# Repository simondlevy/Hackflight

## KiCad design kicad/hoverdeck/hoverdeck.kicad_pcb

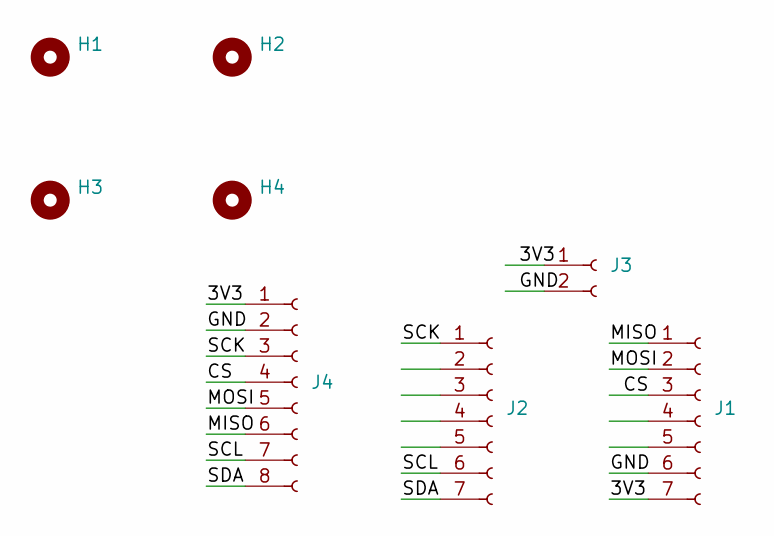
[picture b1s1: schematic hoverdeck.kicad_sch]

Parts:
H1, H2, H3, H4: MountingHole; MountingHole_2.5mm
J1, J2: Conn_01x07_Socket; PinSocket_1x07_P2.54mm_Vertical
J3: Conn_01x02_Socket; PinSocket_1x02_P2.54mm_Vertical
J4: Conn_01x08_Socket; PinSocket_1x08_P2.00mm_Vertical

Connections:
/3V3: J1.7, J3.1, J4.1
/CS: J1.3, J4.4
/GND: J1.6, J3.2, J4.2
/MISO: J1.1, J4.6
/MOSI: J1.2, J4.5
/SCK: J2.1, J4.3
/SCL: J2.6, J4.7
/SDA: J2.7, J4.8

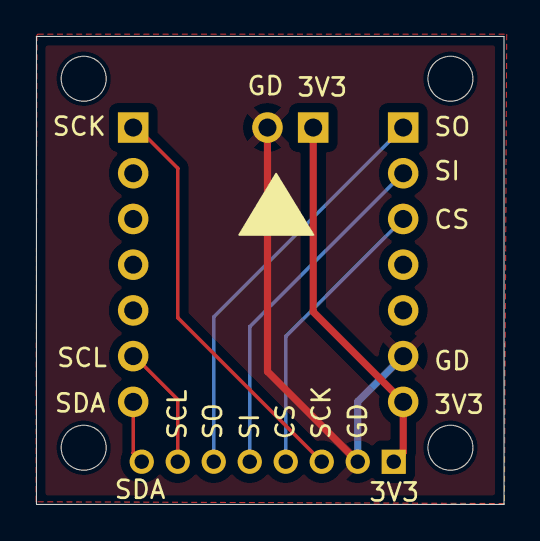
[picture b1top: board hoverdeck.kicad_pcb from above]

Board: 2 copper layers, 26.0 x 26.0 mm, 8 parts (0 on the bottom side), 8 nets.

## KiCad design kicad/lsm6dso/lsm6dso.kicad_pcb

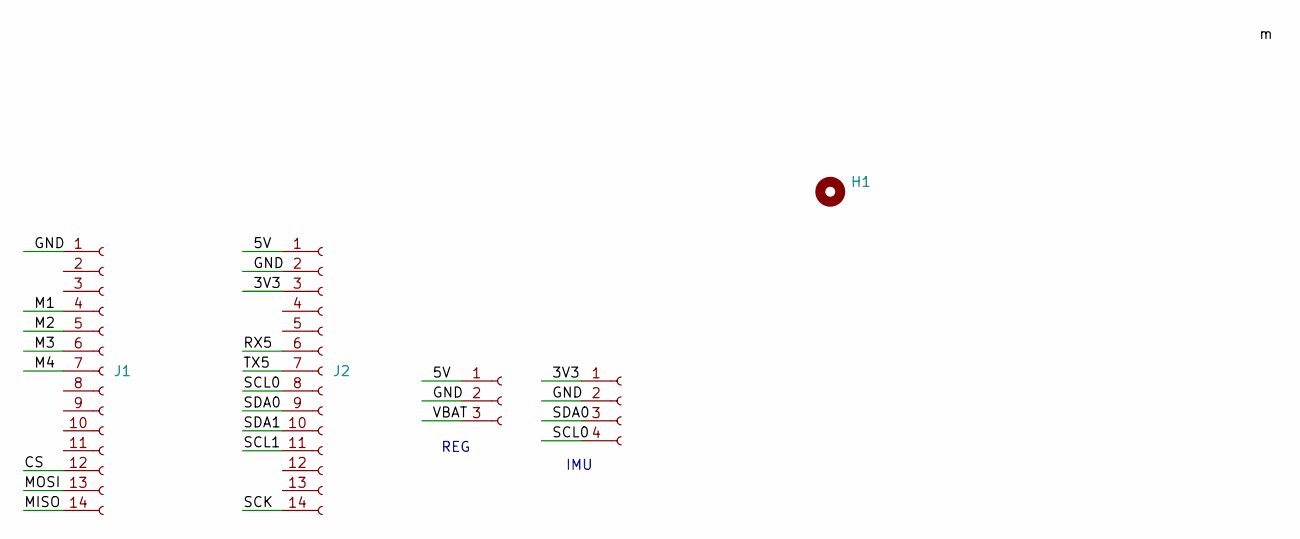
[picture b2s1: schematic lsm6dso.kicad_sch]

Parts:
H1: MountingHole; MountingHole_2.5mm
J1, J2: Conn_01x14_Socket; PinSocket_1x14_P2.54mm_Vertical
J4: Conn_01x03_Socket; PinHeader_1x03_P2.54mm_Vertical
J7: Conn_01x04_Socket; PinHeader_1x04_P2.54mm_Vertical

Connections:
/3V3: J2.3, J7.1
/5V: J2.1, J4.1
/CS: J1.12
/GND: J1.1, J2.2, J4.2, J7.2
/M1: J1.4
/M2: J1.5
/M3: J1.6
/M4: J1.7
/MISO: J1.14
/MOSI: J1.13
/RX5: J2.6
/SCK: J2.14
/SCL0: J2.8, J7.4
/SCL1: J2.11
/SDA0: J2.9, J7.3
/SDA1: J2.10
/TX5: J2.7
/VBAT: J4.3

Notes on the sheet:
REG
IMU

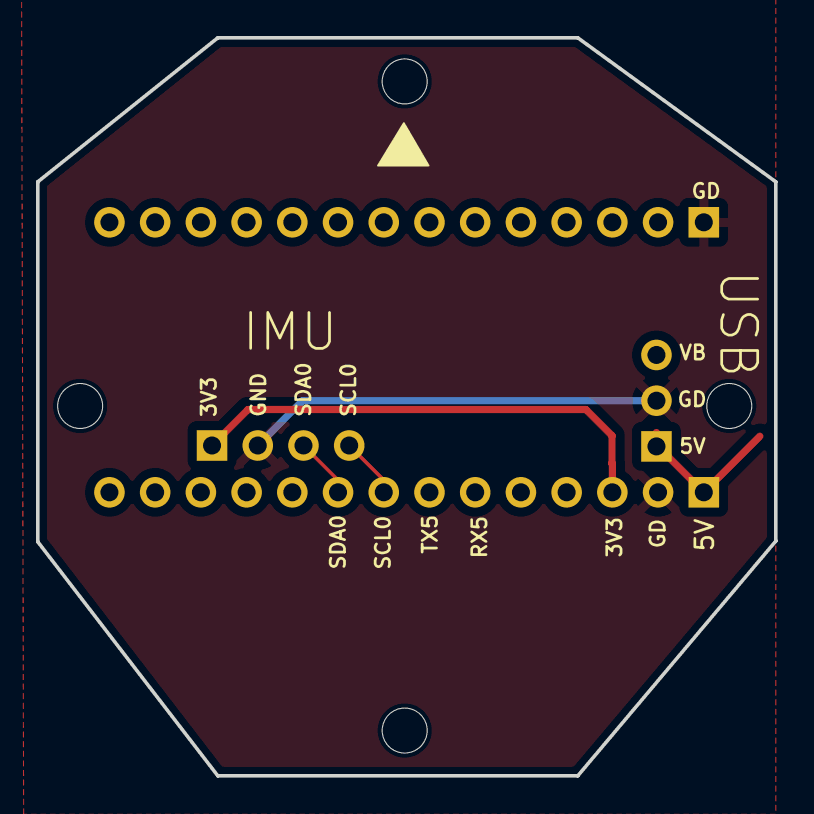
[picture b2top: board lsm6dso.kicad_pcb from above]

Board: 2 copper layers, 41.0 x 41.0 mm, 6 parts (0 on the bottom side), 5 nets.

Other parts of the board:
H1#2: MountingHole; MountingHole_2.5mm

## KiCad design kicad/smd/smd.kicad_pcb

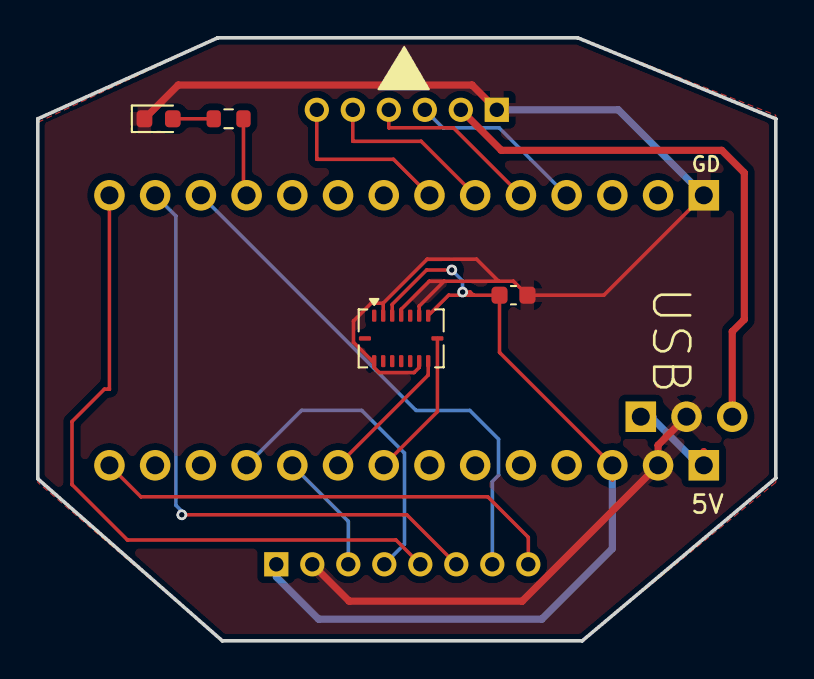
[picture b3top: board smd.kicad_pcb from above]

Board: 2 copper layers, 41.0 x 33.5 mm, 9 parts (0 on the bottom side), 18 nets.

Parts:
C1: C; C_0603_1608Metric
D1: LED; LED_0603_1608Metric
J1: Conn_01x14; PinSocket_1x14_P2.54mm_Vertical
J2: Conn_01x14_Socket; PinSocket_1x14_P2.54mm_Vertical
J4: Conn_01x03_Socket; PinHeader_1x03_P2.54mm_Vertical
J5: Conn_01x06; PinSocket_1x06_P2.00mm_Vertical
J6: Conn_01x08; PinSocket_1x08_P2.00mm_Vertical
R1: R; R_0603_1608Metric
U1: BMI088; Bosch_LGA-16_4.5x3mm_P0.5mm_LayoutBorder7x1y_ClockwisePinNu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

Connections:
/3V3: C1.2, J2.3, J6.1, U1.3 (VDD), U1.7 (PS)
/5V: J2.1, J4.1
/CS: J1.12, J6.7
/GND: C1.1, D1.1 (K), J1.1, J2.2, J4.2, J5.1, J6.2, U1.2 (GNDA), U1.4 (GNDA), U1.6 (GNDIO), U1.10 (SDO2), U1.15 (SDO1)
/LED: J1.11, R1.2
/M1: J1.4, J5.3
/M2: J1.5, J5.4
/M3: J1.6, J5.5
/M4: J1.7, J5.6
/MISO: J1.14, J6.5
/MOSI: J1.13, J6.6
/SCK: J2.14, J6.8
/SCL0: J2.8, U1.8 (SCK/SCL)
/SCL1: J2.11, J6.4
/SDA0: J2.9, U1.9 (SDI/SDA)
/SDA1: J2.10, J6.3
/VBAT: J4.3, J5.2
unnamed: D1.2 (A), R1.1

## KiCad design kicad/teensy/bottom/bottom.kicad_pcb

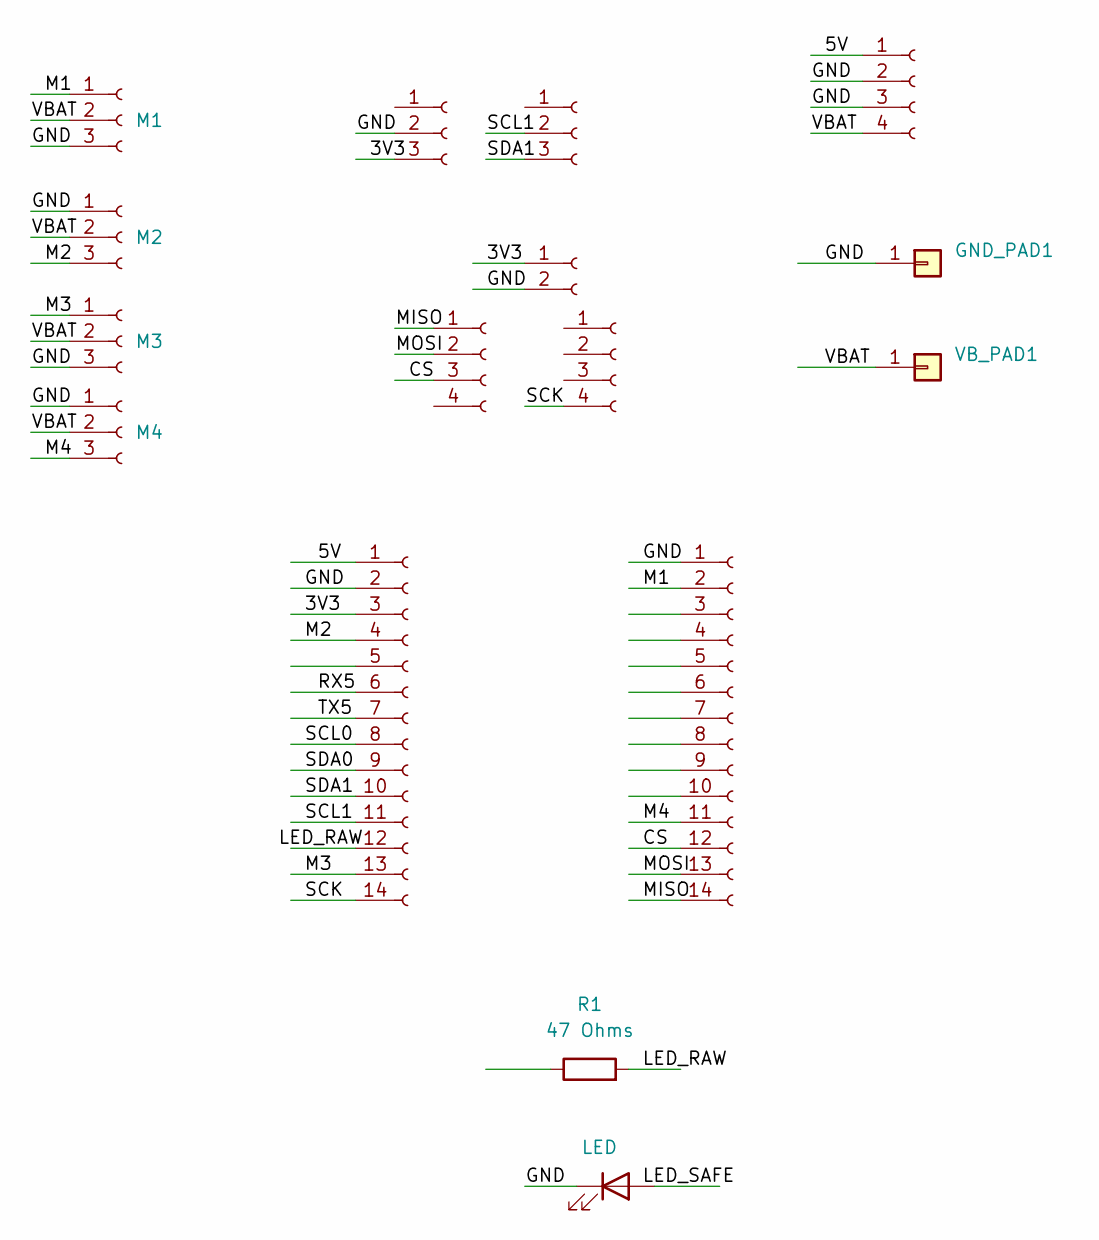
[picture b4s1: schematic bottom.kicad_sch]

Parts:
D1: LED; LED_D3.0mm
GND_PAD1: Conn_01x01; SolderWirePad_1x01_SMD_5x10mm
J1, J6, J8: Conn_01x04_Socket; PinSocket_1x04_P2.54mm_Vertical
J2, J7: Conn_01x03_Socket; PinSocket_1x03_P2.54mm_Vertical
J3: Conn_01x02_Socket; PinSocket_1x02_P2.54mm_Vertical
J4, J5: Conn_01x14_Socket; PinSocket_1x14_P2.54mm_Vertical
M1, M2, M3, M4: Conn_01x03_Socket; PinSocket_1x03_P2.54mm_Vertical
R1: 47 Ohms; R_Axial_DIN0204_L3.6mm_D1.6mm_P5.08mm_Horizontal
VB_PAD1: Conn_01x01; SolderWirePad_1x01_SMD_5x10mm

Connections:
/3V3: J2.3, J3.1, J4.3
/5V: J4.1, J8.1
/CS: J5.12, J6.3
/GND: D1.1 (K), GND_PAD1.1, J2.2, J3.2, J4.2, J5.1, J8.2, J8.3, M1.3, M2.1, M3.3, M4.1
/LED_RAW: R1.2
/M1: J5.2, M1.1
/M2: J4.4, M2.3
/M3: J4.13, M3.1
/M4: J5.11, M4.3
/MISO: J5.14, J6.1
/MOSI: J5.13, J6.2
/RX5: J4.6
/SCK: J1.4, J4.14
/SCL0: J4.8
/SCL1: J4.11, J7.2
/SDA0: J4.9
/SDA1: J4.10, J7.3
/TX5: J4.7
/VBAT: J8.4, M1.2, M2.2, M3.2, M4.2, VB_PAD1.1

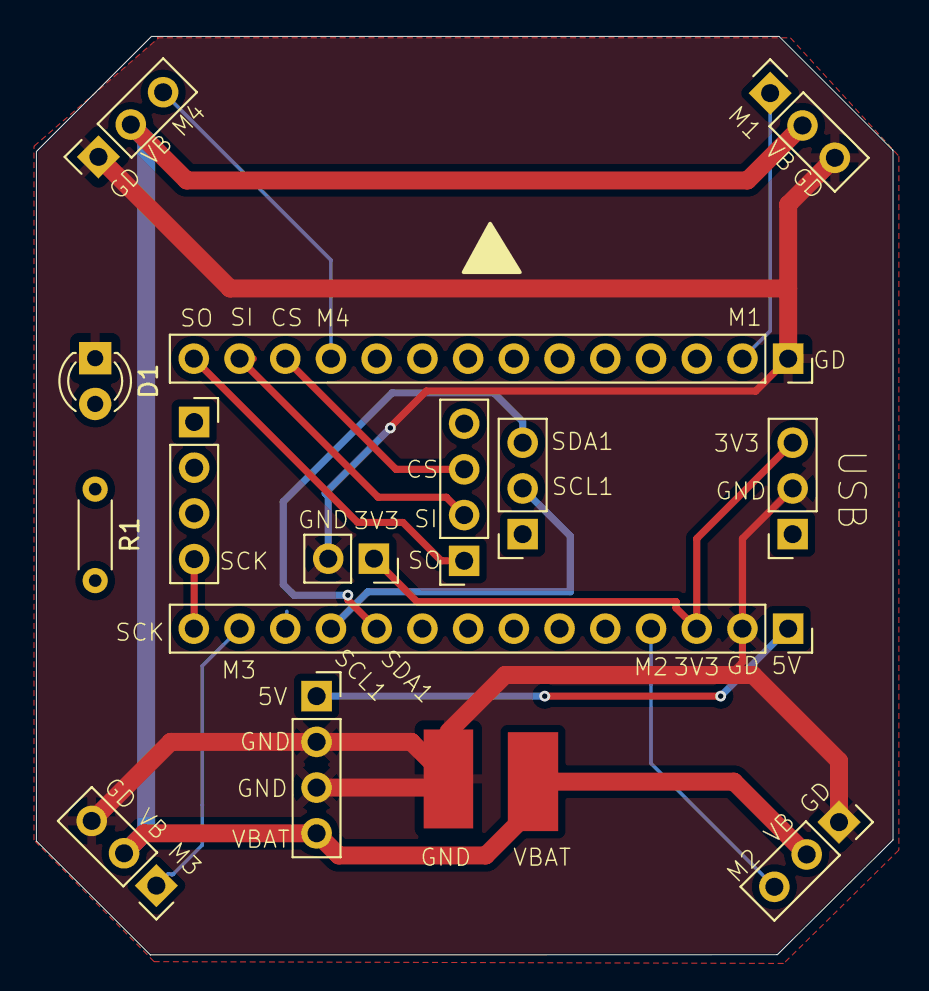
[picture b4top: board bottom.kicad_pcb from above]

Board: 2 copper layers, 47.6 x 51.0 mm, 16 parts (0 on the bottom side), 14 nets.

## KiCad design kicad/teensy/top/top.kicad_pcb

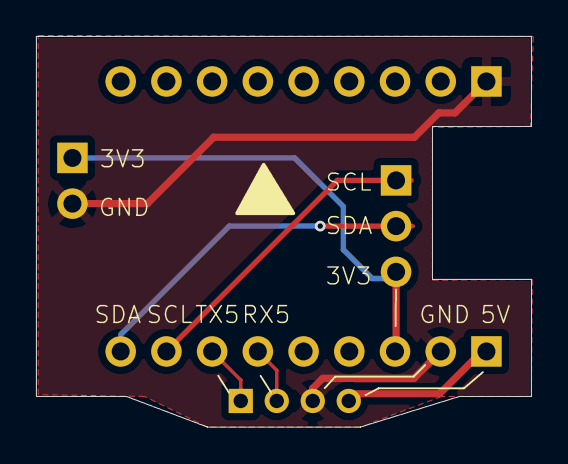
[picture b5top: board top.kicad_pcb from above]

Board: 2 copper layers, 27.5 x 21.7 mm, 5 parts (0 on the bottom side), 7 nets.

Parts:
J1: Conn_01x04_Socket; PinHeader_1x04_P2.00mm_Vertical
J2, J3: Conn_01x09_Socket; PinHeader_1x09_P2.54mm_Vertical
Motor5: Conn_01x03_Female; PinHeader_1x03_P2.54mm_Vertical
PMW3901_PWR2: Conn_01x02_Female; PinHeader_1x02_P2.54mm_Vertical

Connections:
/3V3: J2.3, Motor5.3, PMW3901_PWR2.1
/5V: J1.4, J2.1
/GND: J1.3, J2.2, J3.1, PMW3901_PWR2.2
/RX5: J1.2, J2.6
/SCL0: J2.8, Motor5.1
/SDA0: J2.9, Motor5.2
/TX5: J1.1, J2.7

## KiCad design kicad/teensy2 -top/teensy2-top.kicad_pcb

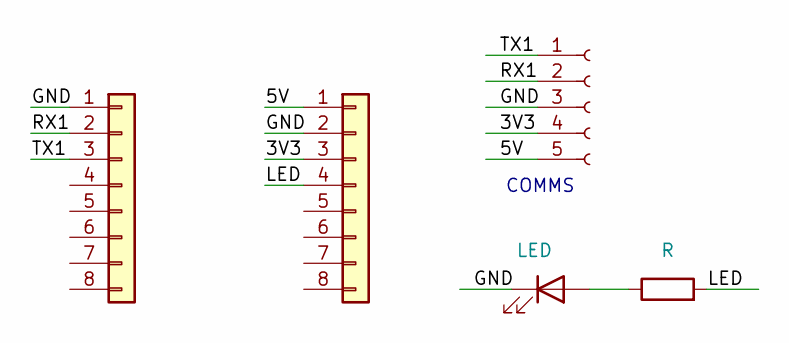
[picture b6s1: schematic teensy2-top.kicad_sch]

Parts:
D1: LED; LED_D3.0mm_FlatTop
J3: Conn_01x05_Socket; PinSocket_1x05_P2.00mm_Vertical
J4, J5: Conn_01x08; PinSocket_1x05_P2.00mm_Vertical
R1: R; R_Axial_DIN0204_L3.6mm_D1.6mm_P5.08mm_Horizontal

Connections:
/3V3: J3.4, J5.3
/5V: J3.5, J5.1
/GND: D1.1 (K), J3.3, J4.1, J5.2
/LED: J5.4, R1.2
/RX1: J3.2, J4.2
/TX1: J3.1, J4.3
unnamed: D1.2 (A), R1.1

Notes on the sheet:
COMMS

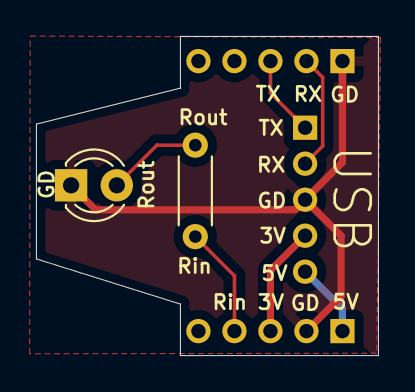
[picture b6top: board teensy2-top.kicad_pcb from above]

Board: 2 copper layers, 19.0 x 17.7 mm, 5 parts (0 on the bottom side), 7 nets.
